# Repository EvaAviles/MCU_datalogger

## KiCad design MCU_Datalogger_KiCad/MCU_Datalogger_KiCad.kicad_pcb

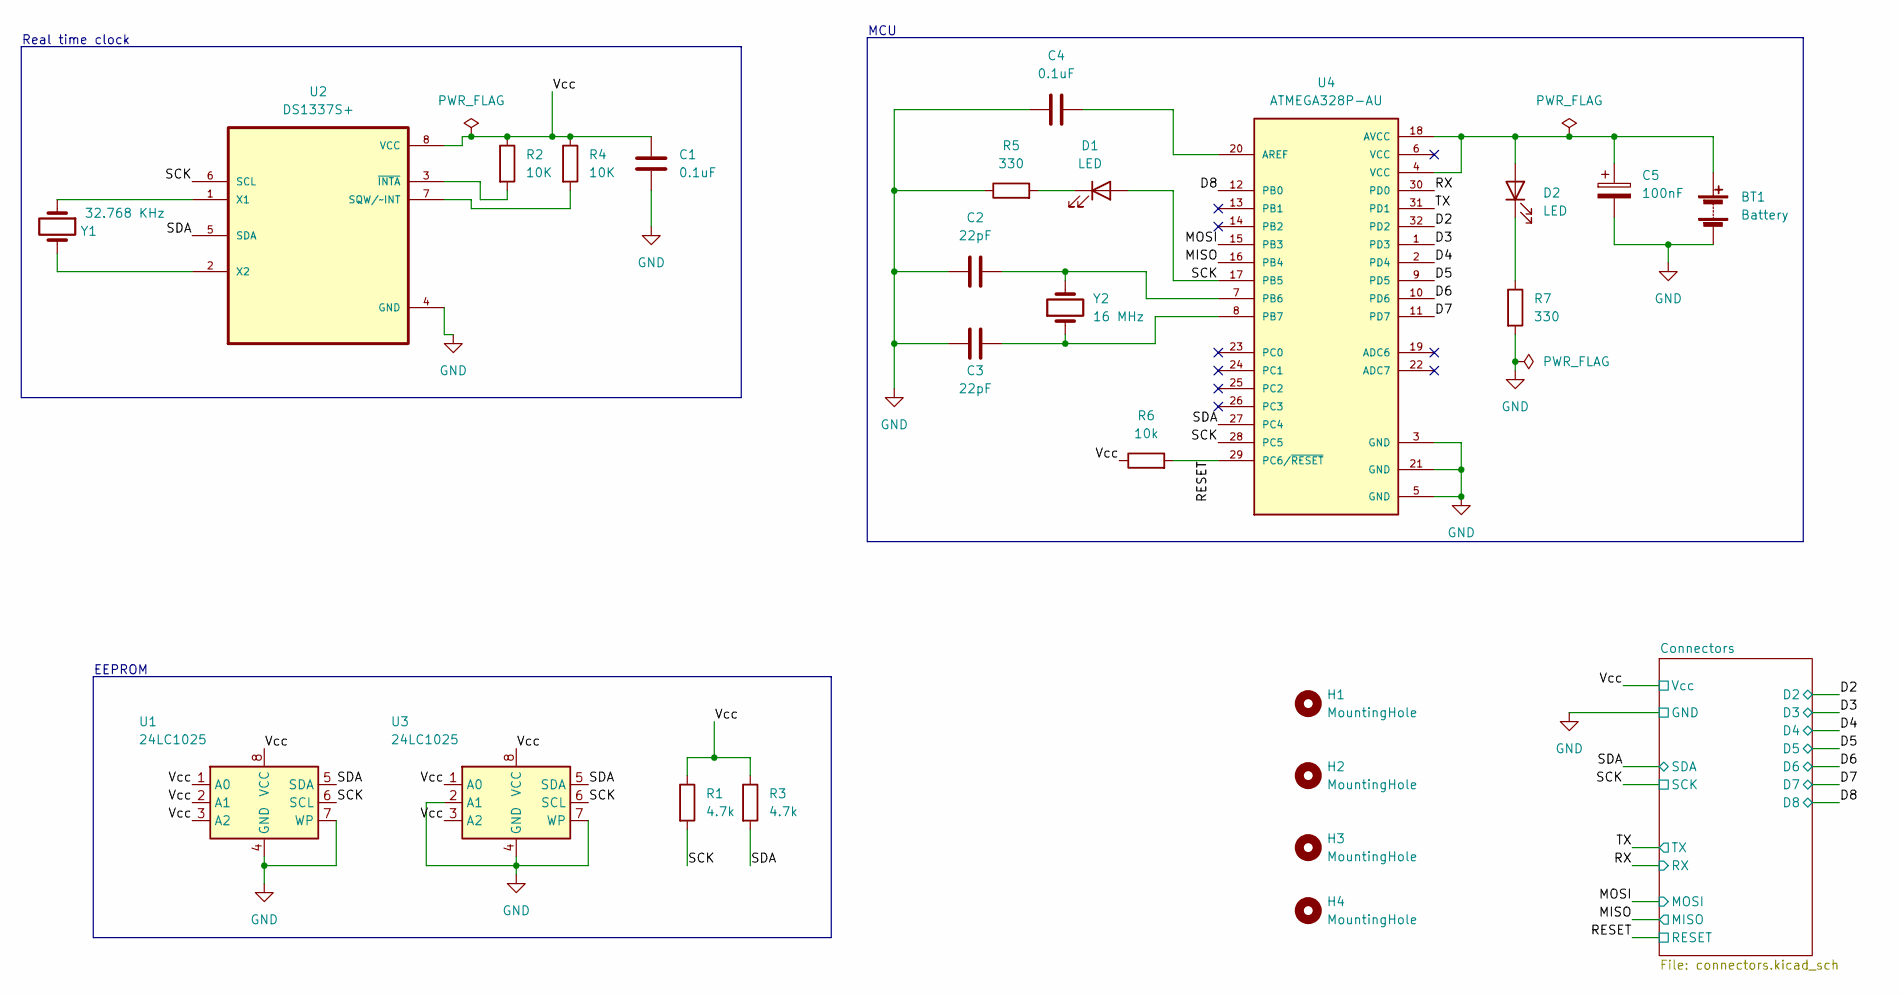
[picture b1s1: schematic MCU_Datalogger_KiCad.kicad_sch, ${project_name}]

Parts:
BT1: Battery; PinHeader_1x02_P2.54mm_Vertical
C1, C4: 0.1uF; C_0805_2012Metric
C2, C3: 22pF; C_0805_2012Metric
C5: 100nF; C_0805_2012Metric
D1, D2: LED; LED_0805_2012Metric
H1, H2, H3, H4: MountingHole; MountingHole_2.1mm
R1, R3: 4.7k; R_0805_2012Metric
R2, R4: 10K; R_0805_2012Metric
R5, R7: 330; R_0805_2012Metric
R6: 10k; R_0805_2012Metric
U1, U3: 24LC1025; SOIC-8_5.23x5.23mm_P1.27mm
U2: DS1337S+; SOIC127P600X175-8N
U4: ATMEGA328P-AU; QFP80P900X900X120-32N
Y1: 32.768 KHz; Crystal_SMD_5032-2Pin_5.0x3.2mm_HandSoldering
Y2: 16 MHz; Crystal_SMD_5032-2Pin_5.0x3.2mm_HandSoldering

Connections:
/D2: U4.32 (PD2); also elsewhere on the board
/D3: U4.1 (PD3); also elsewhere on the board
/D4: U4.2 (PD4); also elsewhere on the board
/D5: U4.9 (PD5); also elsewhere on the board
/D6: U4.10 (PD6); also elsewhere on the board
/D7: U4.11 (PD7); also elsewhere on the board
/D8: U4.12 (PB0); also elsewhere on the board
/MISO: U4.16 (PB4); also elsewhere on the board
/MOSI: U4.15 (PB3); also elsewhere on the board
/RESET: R6.2, U4.29 (PC6/~RESET); also elsewhere on the board
/RX: U4.30 (PD0); also elsewhere on the board
/SCK: D1.2 (A), R1.2, U1.6 (SCL), U2.6 (SCL), U3.6 (SCL), U4.17 (PB5), U4.28 (PC5); also elsewhere on the board
/SDA: R3.2, U1.5 (SDA), U2.5 (SDA), U3.5 (SDA), U4.27 (PC4); also elsewhere on the board
/TX: U4.31 (PD1); also elsewhere on the board
/Vcc: C1.1, R1.1, R2.1, R3.1, R4.1, R6.1, U1.1 (A0), U1.2 (A1), U1.3 (A2), U1.8 (VCC), U2.8 (VCC), U3.1 (A0), U3.3 (A2), U3.8 (VCC); also elsewhere on the board
GND: BT1.2 (-), C1.2, C2.1, C3.1, C4.1, C5.2, R5.1, R7.2, U1.4 (GND), U1.7 (WP), U2.4 (GND), U3.2 (A1), U3.4 (GND), U3.7 (WP), U4.3 (GND), U4.5 (GND), U4.21 (GND); also elsewhere on the board
unnamed: BT1.1 (+), C5.1, D2.2 (A), U4.4 (VCC), U4.18 (AVCC)
unnamed: C2.2, U4.7 (PB6), Y2.2
unnamed: C3.2, U4.8 (PB7), Y2.1
unnamed: C4.2, U4.20 (AREF)
unnamed: D1.1 (K), R5.2
unnamed: D2.1 (K), R7.1
unnamed: R2.2, U2.3 (~INTA)
unnamed: R4.2, U2.7 (SQW/~INT)
unnamed: U2.1 (X1), Y1.1
unnamed: U2.2 (X2), Y1.2

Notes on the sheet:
MCU
Real time clock
EEPROM

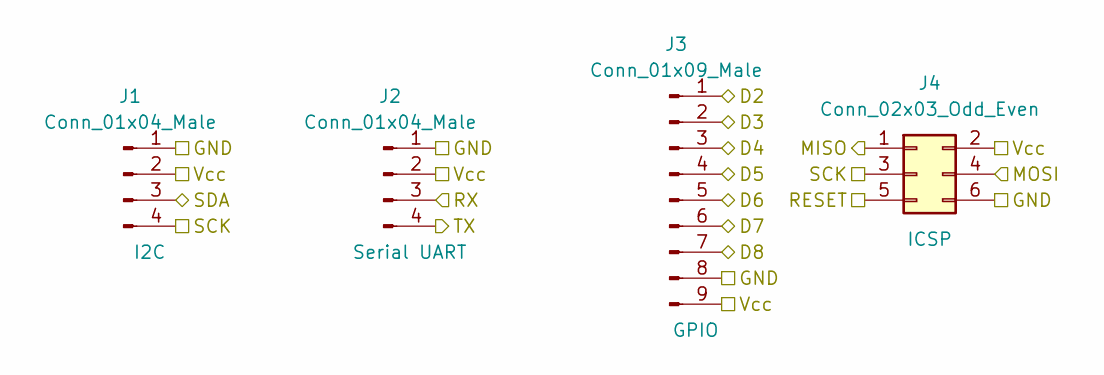
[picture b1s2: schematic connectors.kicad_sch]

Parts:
J1, J2: Conn_01x04_Male; PinHeader_1x04_P2.54mm_Vertical
J3: Conn_01x09_Male; PinHeader_1x09_P2.54mm_Vertical
J4: Conn_02x03_Odd_Even; PinHeader_2x03_P2.54mm_Vertical

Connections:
/D2: J3.1; also elsewhere on the board
/D3: J3.2; also elsewhere on the board
/D4: J3.3; also elsewhere on the board
/D5: J3.4; also elsewhere on the board
/D6: J3.5; also elsewhere on the board
/D7: J3.6; also elsewhere on the board
/D8: J3.7; also elsewhere on the board
/MISO: J4.1; also elsewhere on the board
/MOSI: J4.4; also elsewhere on the board
/RESET: J4.5; also elsewhere on the board
/RX: J2.3; also elsewhere on the board
/SCK: J1.4, J4.3; also elsewhere on the board
/SDA: J1.3; also elsewhere on the board
/TX: J2.4; also elsewhere on the board
/Vcc: J1.2, J2.2, J3.9, J4.2; also elsewhere on the board
GND: J1.1, J2.1, J3.8, J4.6; also elsewhere on the board

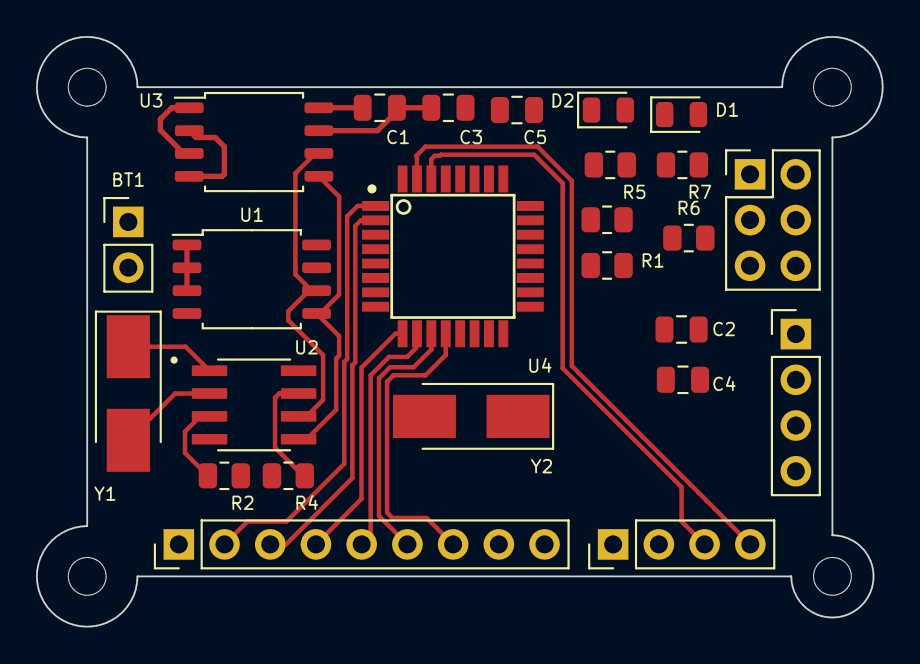
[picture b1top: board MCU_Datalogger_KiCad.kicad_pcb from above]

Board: 4 copper layers, 47.0 x 32.8 mm, 29 parts (0 on the bottom side), 26 nets.

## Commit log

2022-12-28 Creating new project
2022-12-28 Setup of schematic
2022-12-28 Addition of components
2022-12-28 Annotation
2022-12-28 Values of components
2022-12-28 Footprint association
2022-12-28 WIRING sheet 1
2022-12-28 Wiring sheet 2
2022-12-28 Allocating classes to nets GND and Vcc
2022-12-28 Completed comments
2022-12-28 PCB editor setup
2022-12-28 Placement of footprints
2022-12-28 Routing
2022-12-28 Finished routing
2022-12-28 Completed board
2022-12-28 Started but didn't finish the routing
